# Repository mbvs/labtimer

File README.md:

# Labtimer

## Setting up VSCode for embedded development:
- https://github.com/bfxdev/Arduino/tree/master/VSCode

## Microchip Product Page
- https://www.microchip.com/wwwproducts/en/ATmega328

## Makefile Generator:
- https://0xdec.gitlab.io/avr-makefile-generator/#

## 7 Segment Displays Max7219 Driver
- https://adnbr.co.uk/articles/max7219-and-7-segment-displays
- with timer: http://www.ermicro.com/blog/?p=2292

## Multiplexing Buttons:
- https://hackaday.com/2017/05/17/a-few-of-our-favorite-chips-4051-analog-mux/
- https://www.youtube.com/watch?v=OgaeEiHemU4

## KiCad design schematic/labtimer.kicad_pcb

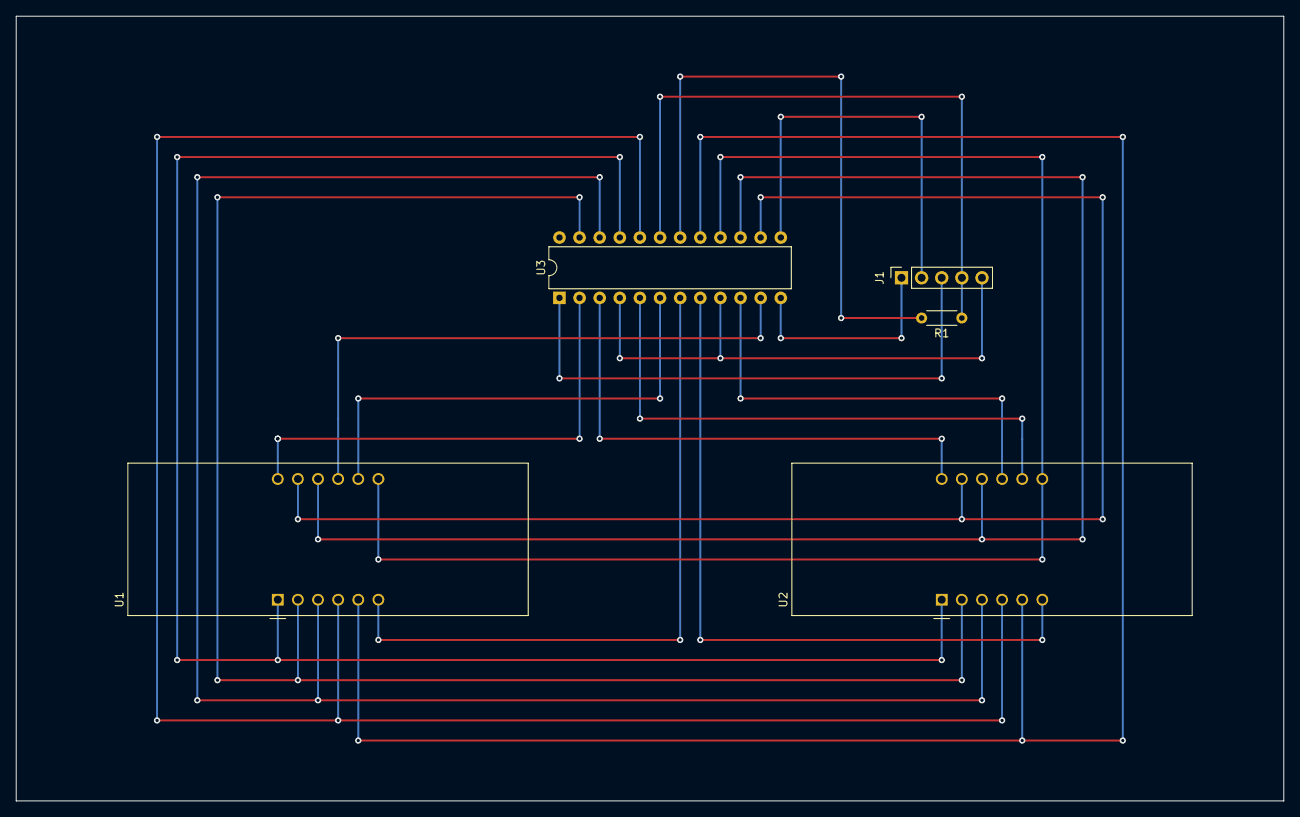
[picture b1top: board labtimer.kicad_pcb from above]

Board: 2 copper layers, 160.0 x 99.1 mm, 5 parts (0 on the bottom side), 22 nets.

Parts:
J1: Conn_01x05; PinSocket_1x05_P2.54mm_Vertical
R1: R; R_Axial_DIN0204_L3.6mm_D1.6mm_P5.08mm_Horizontal
U1, U2: CC56-12SRWA; CA56-12SRWA
U3: MAX7219; DIP-24_W7.62mm

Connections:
+5V: J1.4, R1.1, U3.19
/CLK: J1.2, U3.13
/DIG1: U1.12, U3.2
/DIG2: U1.9, U3.11
/DIG3: U1.8, U3.6
/DIG4: U1.6, U3.7
/DIG5: U2.12, U3.3
/DIG6: U2.9, U3.10
/DIG7: U2.8, U3.5
/DIG8: U2.6, U3.8
/ISET: R1.2, U3.18
/MISO: J1.3, U3.1
/SS: J1.1, U3.12
/SegA: U1.11, U2.11, U3.14
/SegB: U1.7, U2.7, U3.16
/SegC: U1.4, U2.4, U3.20
/SegDP: U1.3, U2.3, U3.22
/SegE: U1.1, U2.1, U3.21
/SegG: U1.5, U2.5, U3.17
/SeqD: U1.2, U2.2, U3.23
/SeqF: U1.10, U2.10, U3.15
GND: J1.5, U3.4, U3.9

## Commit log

2018-10-22 add .gitignore
2018-10-22 add datasheets
2018-10-22 add max7219 datasheet
2018-10-25 add make-file
2018-10-25 rename makefile
2018-10-25 Rename makefile to Makefile
2018-10-25 add main.c
2018-10-25 add .vscode files
2018-10-25 add defines
2019-12-31 configure vscode settings
2019-12-31 add scratchpad
2019-12-31 customize settings
2019-12-31 add build clean and flash tasks
2019-12-31 add blink code
2019-12-31 minor tweak
2020-01-02 add display datasheet
2020-01-03 add links
2020-01-03 add diylc schematic
2020-01-04 update infos
2020-01-04 gitconfig test
2020-01-18 add kicad schematics
